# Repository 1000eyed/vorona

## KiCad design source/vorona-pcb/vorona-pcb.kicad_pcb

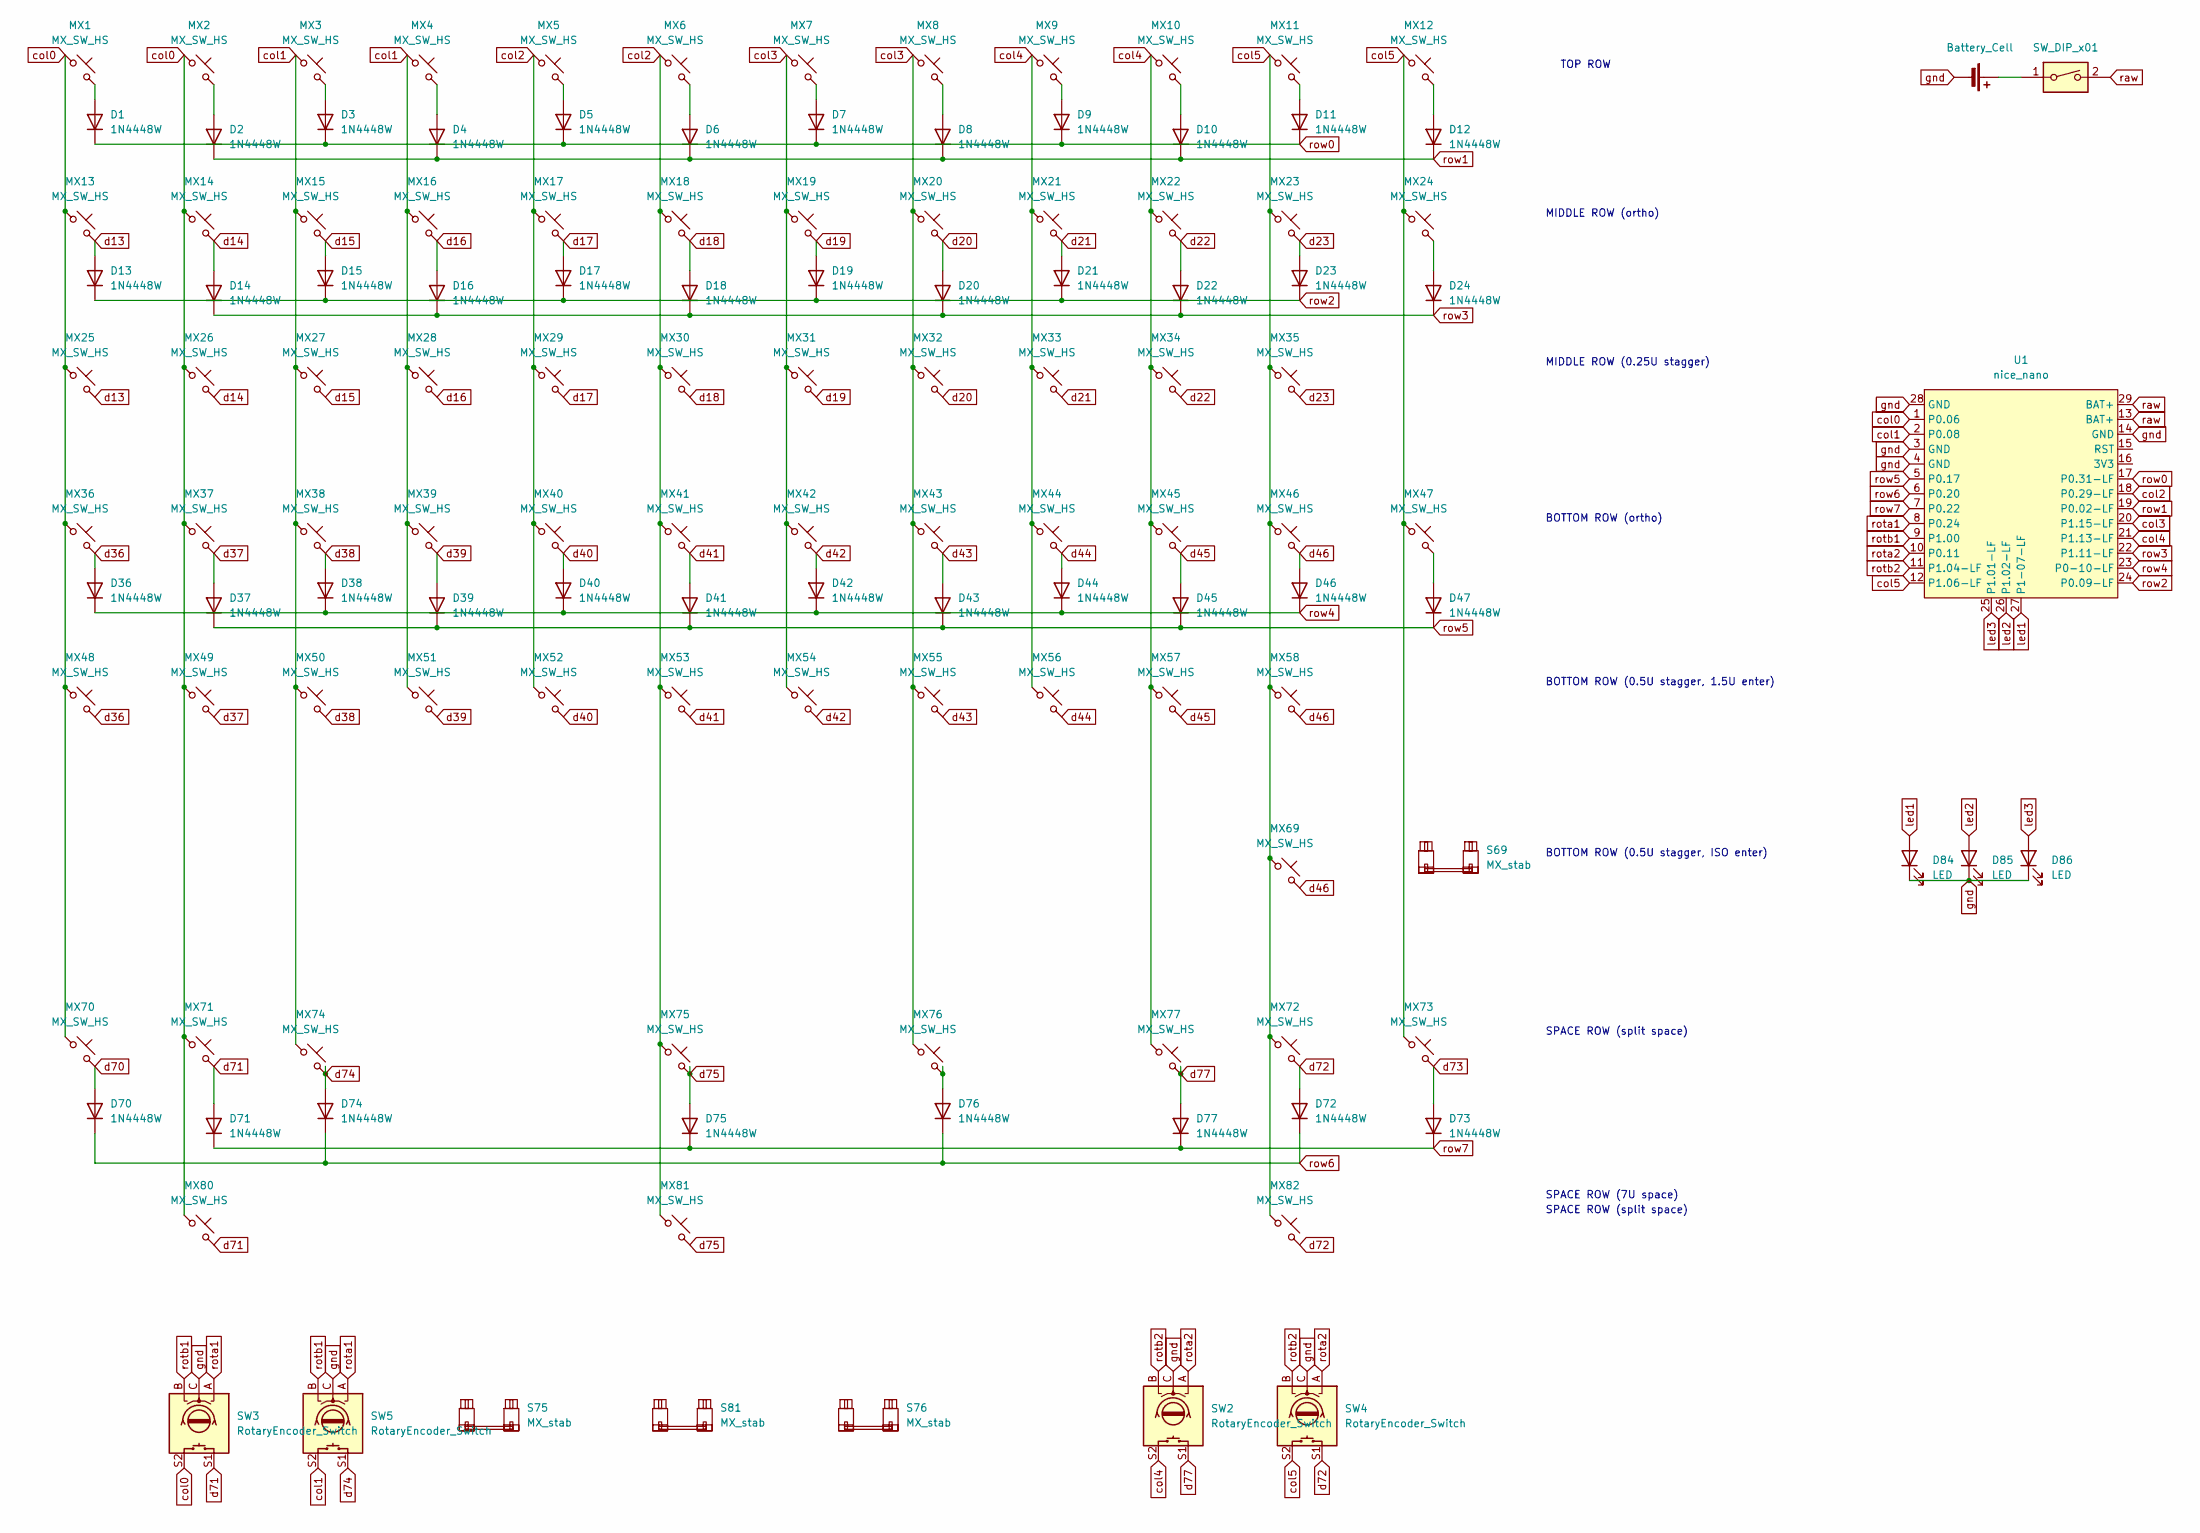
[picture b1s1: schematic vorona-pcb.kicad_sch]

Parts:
BT1: Battery_Cell; JST_PH_S2B-PH-K_1x02_P2.00mm_Horizontal
D1, D2, D3, D4, D5, D6, D7, D8, D9, D10, D11, D12, D13, D14, D15, D16, D17, D18, D19, D20, D21, D22, D23, D24, D36, D37, D38, D39, D40, D41, D42, D43, D44, D45, D46, D47, D70, D71, D72, D73, D74, D75, D76, D77: 1N4448W; D_SOD-123 invisible designator
D84, D85, D86: LED; LED_D3.0mm
MX1, MX2, MX3, MX4, MX8, MX9, MX10, MX11, MX12, MX13, MX14, MX15, MX16, MX17, MX18, MX19, MX20, MX21, MX22, MX23, MX24, MX25, MX26, MX27, MX28, MX29, MX30, MX31, MX32, MX33, MX34, MX35, MX36, MX37, MX38, MX39, MX40, MX41, MX42, MX43, MX44, MX45, MX46, MX47, MX48, MX49, MX50, MX51, MX52, MX53, MX54, MX55, MX56, MX57, MX58, MX69, MX70, MX71, MX72, MX73, MX74, MX75, MX76, MX77, MX80, MX81, MX82: MX_SW_HS; SW_MX_HS_S_1u_invisible_designator
MX5, MX6, MX7: MX_SW_HS; SW_MX_1u
S69: MX_stab; STAB_MX_ISO
S75: MX_stab; STAB_MX_P_2.75u
S76: MX_stab; STAB_MX_P_2.25u
S81: MX_stab; STAB_MX_P_7u
SW1: SW_DIP_x01; SW_MSK12C02-HB
SW2, SW3, SW4, SW5: RotaryEncoder_Switch; ROT_Alps_EC11E-Switch
U1: nice_nano; nice_nano_AH_USBup

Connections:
unnamed: BT1.1 (+), SW1.1
unnamed: D1.2 (A), MX1.2
unnamed: D2.2 (A), MX2.2
unnamed: D3.2 (A), MX3.2
unnamed: D4.2 (A), MX4.2
unnamed: D5.2 (A), MX5.2
unnamed: D6.2 (A), MX6.2
unnamed: D7.2 (A), MX7.2
unnamed: D8.2 (A), MX8.2
unnamed: D9.2 (A), MX9.2
unnamed: D10.2 (A), MX10.2
unnamed: D11.2 (A), MX11.2
unnamed: D12.2 (A), MX12.2
unnamed: D24.2 (A), MX24.2
unnamed: D47.2 (A), MX47.2
unnamed: D76.2 (A), MX76.2
col0: MX1.1, MX2.1, MX13.1, MX14.1, MX25.1, MX26.1, MX36.1, MX37.1, MX48.1, MX49.1, MX70.1, MX71.1, MX80.1, SW3.S2, U1.1 (P0.06)
col1: MX3.1, MX4.1, MX15.1, MX16.1, MX27.1, MX28.1, MX38.1, MX39.1, MX50.1, MX51.1, MX74.1, SW5.S2, U1.2 (P0.08)
col2: MX5.1, MX6.1, MX17.1, MX18.1, MX29.1, MX30.1, MX40.1, MX41.1, MX52.1, MX53.1, MX75.1, MX81.1, U1.18 (P0.29-LF)
col3: MX7.1, MX8.1, MX19.1, MX20.1, MX31.1, MX32.1, MX42.1, MX43.1, MX54.1, MX55.1, MX76.1, U1.20 (P1.15-LF)
col4: MX9.1, MX10.1, MX21.1, MX22.1, MX33.1, MX34.1, MX44.1, MX45.1, MX56.1, MX57.1, MX77.1, SW2.S2, U1.21 (P1.13-LF)
col5: MX11.1, MX12.1, MX23.1, MX24.1, MX35.1, MX46.1, MX47.1, MX58.1, MX69.1, MX72.1, MX73.1, MX82.1, SW4.S2, U1.12 (P1.06-LF)
d13: D13.2 (A), MX13.2, MX25.2
d14: D14.2 (A), MX14.2, MX26.2
d15: D15.2 (A), MX15.2, MX27.2
d16: D16.2 (A), MX16.2, MX28.2
d17: D17.2 (A), MX17.2, MX29.2
d18: D18.2 (A), MX18.2, MX30.2
d19: D19.2 (A), MX19.2, MX31.2
d20: D20.2 (A), MX20.2, MX32.2
d21: D21.2 (A), MX21.2, MX33.2
d22: D22.2 (A), MX22.2, MX34.2
d23: D23.2 (A), MX23.2, MX35.2
d36: D36.2 (A), MX36.2, MX48.2
d37: D37.2 (A), MX37.2, MX49.2
d38: D38.2 (A), MX38.2, MX50.2
d39: D39.2 (A), MX39.2, MX51.2
d40: D40.2 (A), MX40.2, MX52.2
d41: D41.2 (A), MX41.2, MX53.2
d42: D42.2 (A), MX42.2, MX54.2
d43: D43.2 (A), MX43.2, MX55.2
d44: D44.2 (A), MX44.2, MX56.2
d45: D45.2 (A), MX45.2, MX57.2
d46: D46.2 (A), MX46.2, MX58.2, MX69.2
d70: D70.2 (A), MX70.2
d71: D71.2 (A), MX71.2, MX80.2, SW3.S1
d72: D72.2 (A), MX72.2, MX82.2, SW4.S1
d73: D73.2 (A), MX73.2
d74: D74.2 (A), MX74.2, SW5.S1
d75: D75.2 (A), MX75.2, MX81.2
d77: D77.2 (A), MX77.2, SW2.S1
gnd: BT1.2 (-), D84.1 (K), D85.1 (K), D86.1 (K), SW2.C, SW3.C, SW4.C, SW5.C, U1.3 (GND), U1.4 (GND), U1.14 (GND), U1.28 (GND)
led1: D84.2 (A), U1.27 (P1-07-LF)
led2: D85.2 (A), U1.26 (P1.02-LF)
led3: D86.2 (A), U1.25 (P1.01-LF)
raw: SW1.2, U1.13 (BAT+), U1.29 (BAT+)
rota1: SW3.A, SW5.A, U1.8 (P0.24)
rota2: SW2.A, SW4.A, U1.10 (P0.11)
rotb1: SW3.B, SW5.B, U1.9 (P1.00)
rotb2: SW2.B, SW4.B, U1.11 (P1.04-LF)
row0: D1.1 (K), D3.1 (K), D5.1 (K), D7.1 (K), D9.1 (K), D11.1 (K), U1.17 (P0.31-LF)
row1: D2.1 (K), D4.1 (K), D6.1 (K), D8.1 (K), D10.1 (K), D12.1 (K), U1.19 (P0.02-LF)
row2: D13.1 (K), D15.1 (K), D17.1 (K), D19.1 (K), D21.1 (K), D23.1 (K), U1.24 (P0.09-LF)
row3: D14.1 (K), D16.1 (K), D18.1 (K), D20.1 (K), D22.1 (K), D24.1 (K), U1.22 (P1.11-LF)
row4: D36.1 (K), D38.1 (K), D40.1 (K), D42.1 (K), D44.1 (K), D46.1 (K), U1.23 (P0-10-LF)
row5: D37.1 (K), D39.1 (K), D41.1 (K), D43.1 (K), D45.1 (K), D47.1 (K), U1.5 (P0.17)
row6: D70.1 (K), D72.1 (K), D74.1 (K), D76.1 (K), U1.6 (P0.20)
row7: D71.1 (K), D73.1 (K), D75.1 (K), D77.1 (K), U1.7 (P0.22)

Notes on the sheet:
MIDDLE ROW (ortho)
BOTTOM ROW (0.5U stagger, 1.5U enter)
MIDDLE ROW (0.25U stagger)
SPACE ROW (7U space)
SPACE ROW (split space)
TOP ROW
BOTTOM ROW (ortho)
BOTTOM ROW (0.5U stagger, ISO enter)

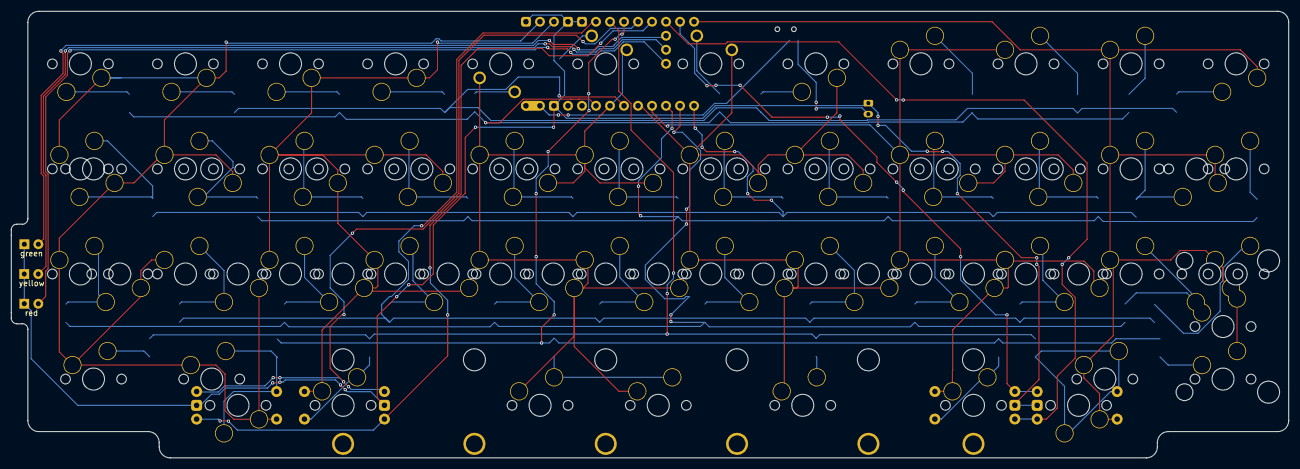
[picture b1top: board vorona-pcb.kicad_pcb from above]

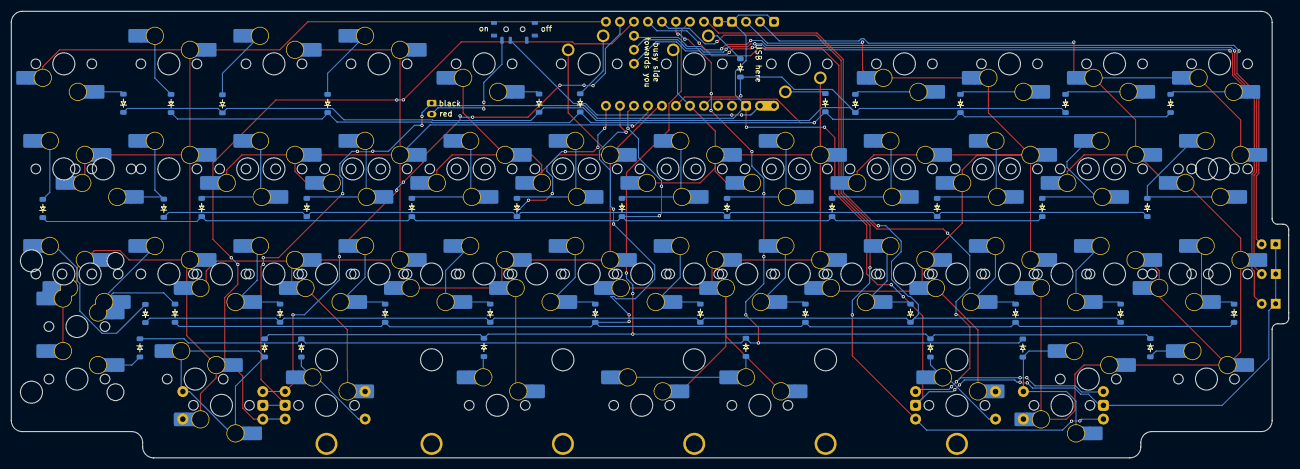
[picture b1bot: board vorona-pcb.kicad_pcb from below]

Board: 2 copper layers, 231.6 x 81.0 mm, 128 parts (117 on the bottom side), 68 nets.
